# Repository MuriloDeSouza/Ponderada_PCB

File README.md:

# Projeto de Criação de PCB com Raspberry Pi Pico

## Descrição do Projeto

Este projeto consiste na criação de uma PCB (Placa de Circuito Impresso) utilizando o microcontrolador Raspberry Pi Pico, um transistor para controlar um LED e dois resistores de 10kΩ. O objetivo principal é criar um circuito simples, porém funcional, que possa ser utilizado como base para projetos mais complexos.

## Estrutura de Diretórios

O repositório está organizado da seguinte forma:

- **Esquemático:**
  - `ponderada_semana_8.kicad_pro.sch`: Arquivo contendo o esquemático do projeto. Este arquivo descreve a conexão entre os componentes utilizados na PCB.

- **PCB:**
  - `ponderada_semana_8.kicad_pcb`: Arquivo contendo o layout da PCB. Aqui estão dispostas as trilhas e componentes da placa de circuito impresso.

- **Fabricação:**
  - Arquivos necessários para a fabricação da placa no laboratório. Estes podem incluir arquivos para a produção do layout, como o gerber, entre outros.

## Sobre o Circuito

O circuito projetado utiliza o Raspberry Pi Pico como controlador principal. O transistor é utilizado para controlar a corrente que passa pelo LED, permitindo assim o controle do seu brilho ou ligar/desligar. Os resistores de 10kΩ são utilizados para limitar a corrente em certas partes do circuito, garantindo seu correto funcionamento e prevenindo danos aos componentes.

Este projeto serve como uma introdução ao design de PCBs e ao uso de microcontroladores em projetos eletrônicos. A partir deste circuito básico, é possível expandir e criar projetos mais complexos, adicionando sensores, módulos de comunicação, entre outros componentes, de acordo com as necessidades específicas de cada aplicação.

## Autor

Desenvolvido por Murilo de Souza Prianti Silva

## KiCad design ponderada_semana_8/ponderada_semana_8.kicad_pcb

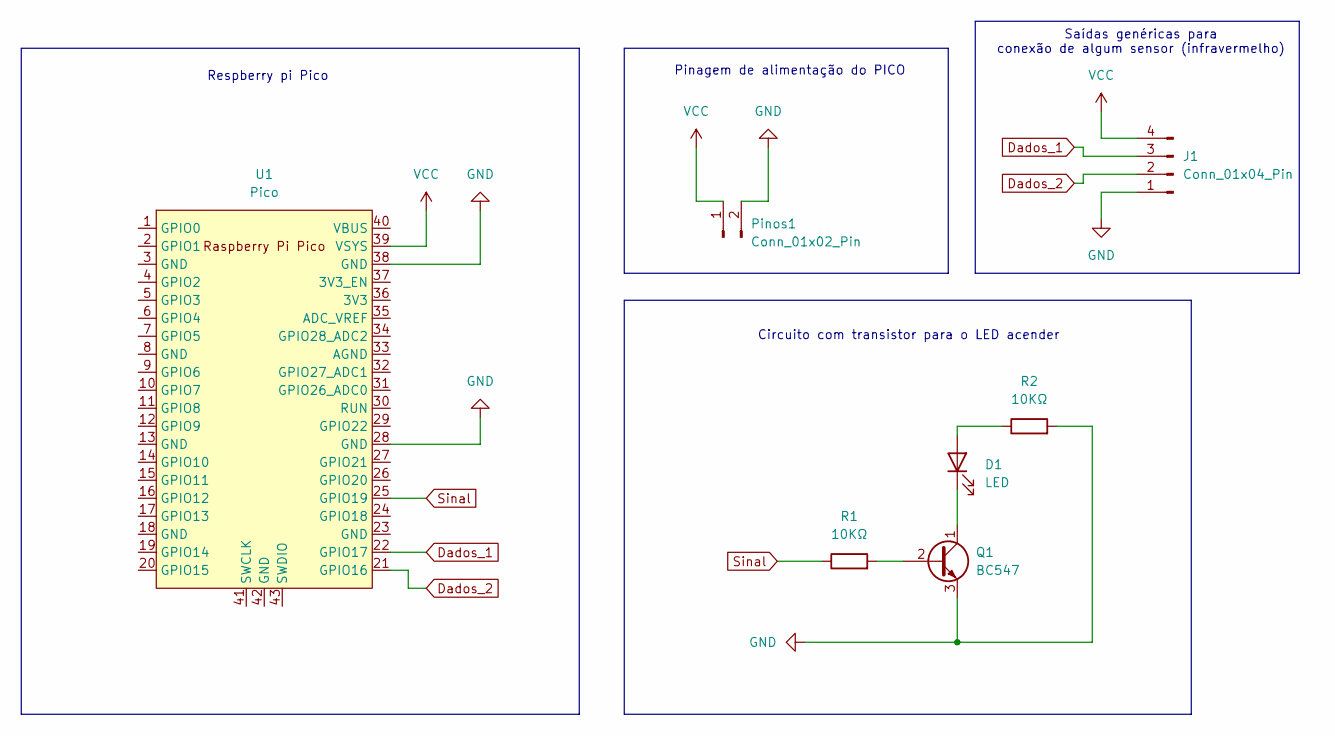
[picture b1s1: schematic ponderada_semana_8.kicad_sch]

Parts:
D1: LED; LED_D5.0mm_Clear
J1: Conn_01x04_Pin; PinHeader_1x04_P2.54mm_Vertical
Pinos1: Conn_01x02_Pin; PinHeader_1x02_P1.27mm_Vertical
Q1: BC547; TO-92L_Inline
R1, R2: 10KΩ; R_Axial_DIN0204_L3.6mm_D1.6mm_P5.08mm_Horizontal
U1: Pico; RPi_Pico_SMD_TH

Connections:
Dados_1: J1.3, U1.22 (GPIO17)
Dados_2: J1.2, U1.21 (GPIO16)
GND: J1.1, Pinos1.2, Q1.3 (E), R2.2, U1.28 (GND), U1.38 (GND)
unnamed: D1.2 (A), R2.1
unnamed: D1.1 (K), Q1.1 (C)
unnamed: Q1.2 (B), R1.2
Sinal: R1.1, U1.25 (GPIO19)
VCC: J1.4, Pinos1.1, U1.39 (VSYS)

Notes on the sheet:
Pinagem de alimentação do PICO
Circuito com transistor para o LED acender
Respberry pi Pico
Saídas genéricas para conexão de algum sensor (infravermelho)

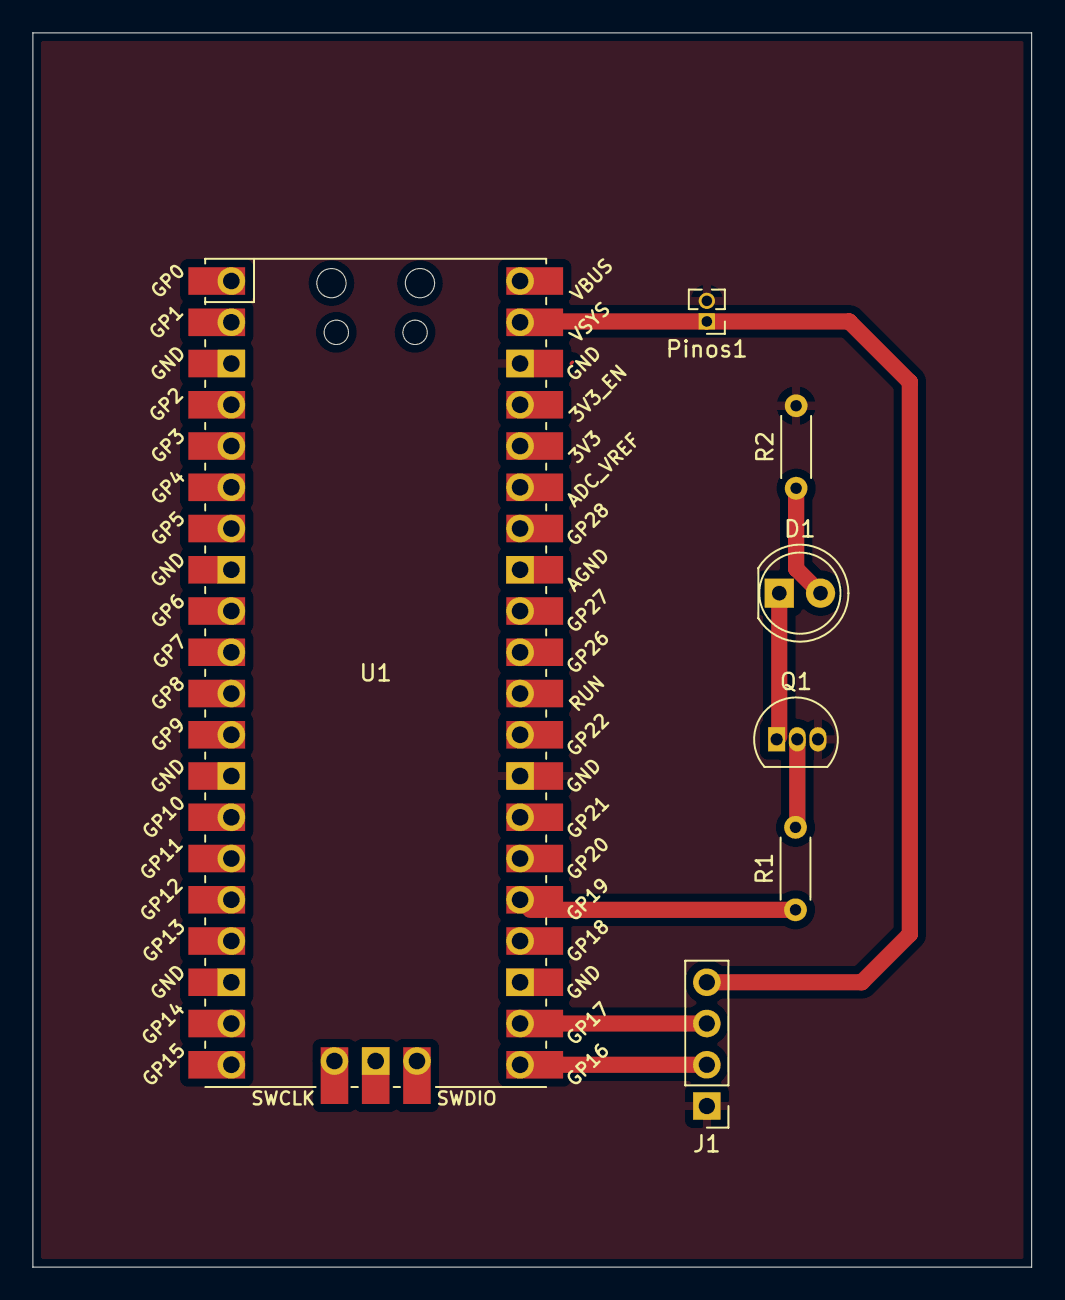
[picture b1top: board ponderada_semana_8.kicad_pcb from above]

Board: 2 copper layers, 61.5 x 76.0 mm, 7 parts (0 on the bottom side), 8 nets.

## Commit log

2024-03-28 add archives from my pc
2024-03-28 att archives
2024-04-02 att_informations
